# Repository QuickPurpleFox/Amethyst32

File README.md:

# Amethyst32
6502 based computer with 32kb of ram memory, with video based on tms9918 and sound on ym3812

## License

[MIT](https://choosealicense.com/licenses/mit/)

## Authors

- [@QuickPurpleFox](https://github.com/QuickPurpleFox) | Daniel K

supported by

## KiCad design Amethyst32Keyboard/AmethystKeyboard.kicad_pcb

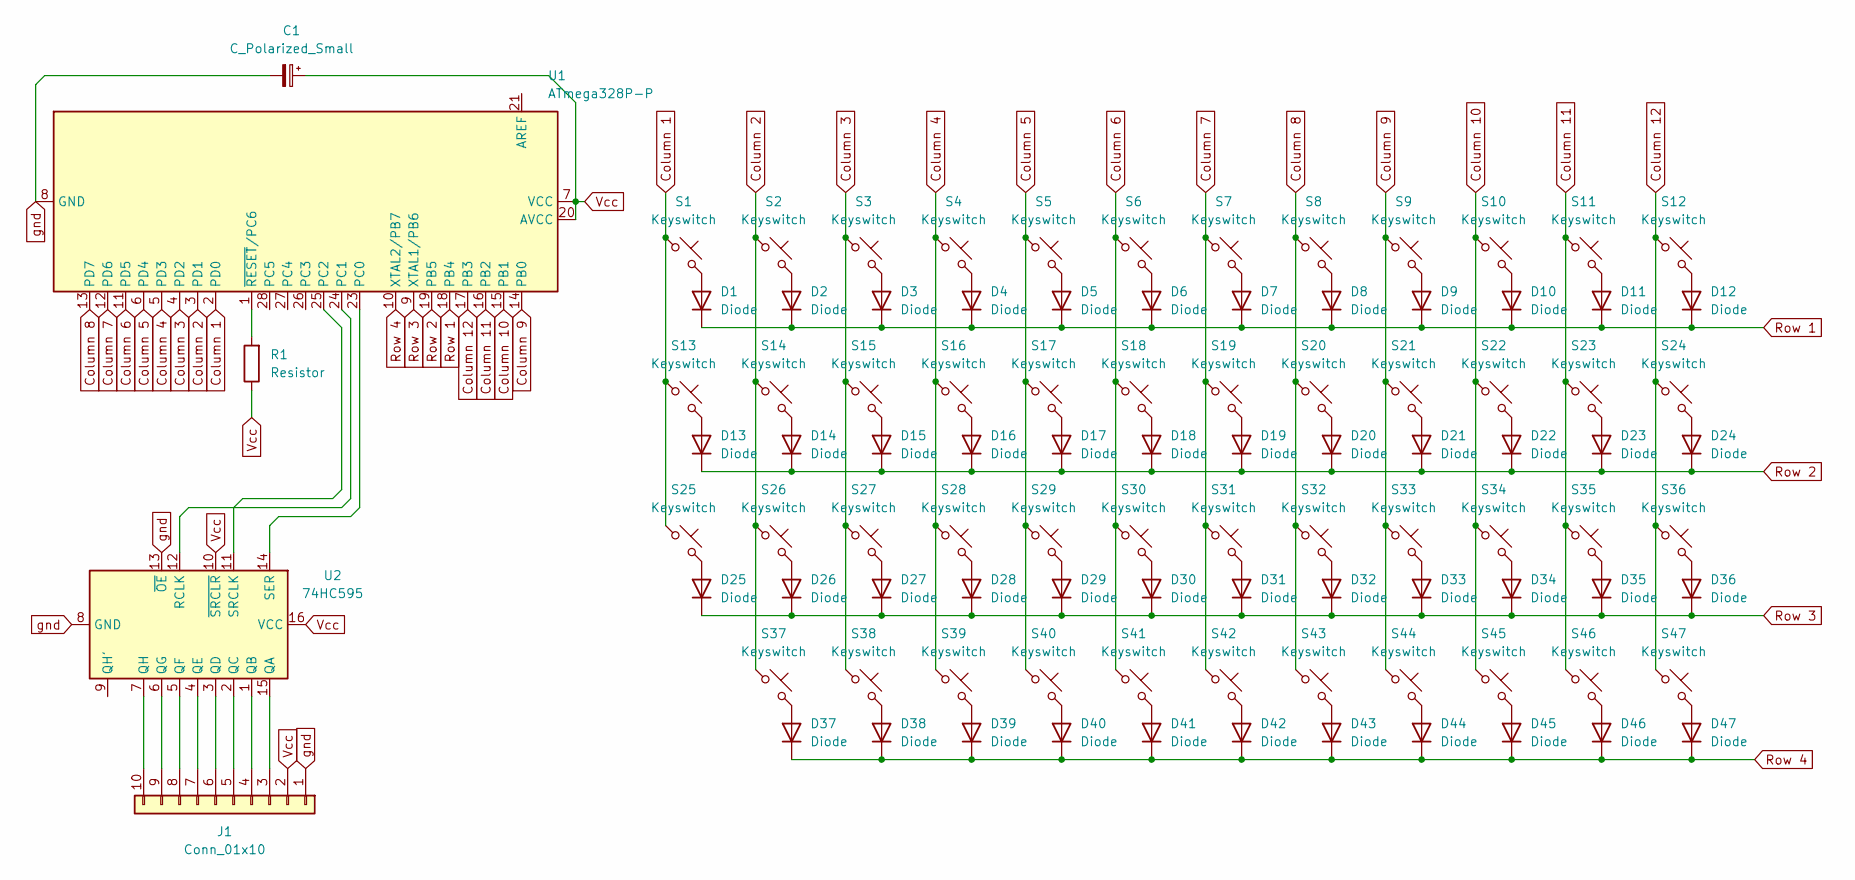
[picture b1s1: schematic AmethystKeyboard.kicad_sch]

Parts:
C1: C_Polarized_Small; CP_Radial_D5.0mm_P2.50mm
D1, D2, D3, D4, D5, D6, D7, D8, D9, D10, D11, D12, D13, D14, D15, D16, D17, D18, D19, D20, D21, D22, D23, D24, D25, D26, D27, D28, D29, D30, D31, D32, D33, D34, D35, D36, D37, D38, D39, D40, D41, D42, D43, D44, D45, D46, D47: Diode; Diode_DO-35
J1: Conn_01x10; PinHeader_1x10_P2.54mm_Vertical
R1: Resistor; R_Axial_DIN0207_L6.3mm_D2.5mm_P7.62mm_Horizontal
S1, S2, S3, S4, S5, S6, S7, S8, S9, S10, S11, S12, S13, S14, S15, S16, S17, S18, S19, S20, S21, S22, S23, S24, S25, S26, S27, S28, S29, S30, S31, S32, S33, S34, S35, S36, S38, S39, S40, S41, S42, S43, S44, S45, S46, S47: Keyswitch; MX_PCB_1.00u
S37: Keyswitch; MX_PCB_2.00u
U1: ATmega328P-P; DIP-28_W7.62mm
U2: 74HC595; DIP-16_W7.62mm

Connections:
Column 1: S1.1, S13.1, S25.1, U1.2 (PD0)
Column 2: S2.1, S14.1, S26.1, S37.1, U1.3 (PD1)
Column 3: S3.1, S15.1, S27.1, S38.1, U1.4 (PD2)
Column 4: S4.1, S16.1, S28.1, S39.1, U1.5 (PD3)
Column 5: S5.1, S17.1, S29.1, S40.1, U1.6 (PD4)
Column 6: S6.1, S18.1, S30.1, S41.1, U1.11 (PD5)
Column 7: S7.1, S19.1, S31.1, S42.1, U1.12 (PD6)
Column 8: S8.1, S20.1, S32.1, S43.1, U1.13 (PD7)
Column 9: S9.1, S21.1, S33.1, S44.1, U1.14 (PB0)
Column 10: S10.1, S22.1, S34.1, S45.1, U1.15 (PB1)
Column 11: S11.1, S23.1, S35.1, S46.1, U1.16 (PB2)
Column 12: S12.1, S24.1, S36.1, S47.1, U1.17 (PB3)
unnamed: D1.2 (A), S1.2
unnamed: D2.2 (A), S2.2
unnamed: D3.2 (A), S3.2
unnamed: D4.2 (A), S4.2
unnamed: D5.2 (A), S5.2
unnamed: D6.2 (A), S6.2
unnamed: D7.2 (A), S7.2
unnamed: D8.2 (A), S8.2
unnamed: D9.2 (A), S9.2
unnamed: D10.2 (A), S10.2
unnamed: D11.2 (A), S11.2
unnamed: D12.2 (A), S12.2
unnamed: D13.2 (A), S13.2
unnamed: D14.2 (A), S14.2
unnamed: D15.2 (A), S15.2
unnamed: D16.2 (A), S16.2
unnamed: D17.2 (A), S17.2
unnamed: D18.2 (A), S18.2
unnamed: D19.2 (A), S19.2
unnamed: D20.2 (A), S20.2
unnamed: D21.2 (A), S21.2
unnamed: D22.2 (A), S22.2
unnamed: D23.2 (A), S23.2
unnamed: D24.2 (A), S24.2
unnamed: D25.2 (A), S25.2
unnamed: D26.2 (A), S26.2
unnamed: D27.2 (A), S27.2
unnamed: D28.2 (A), S28.2
unnamed: D29.2 (A), S29.2
unnamed: D30.2 (A), S30.2
unnamed: D31.2 (A), S31.2
unnamed: D32.2 (A), S32.2
unnamed: D33.2 (A), S33.2
unnamed: D34.2 (A), S34.2
unnamed: D35.2 (A), S35.2
unnamed: D36.2 (A), S36.2
unnamed: D37.2 (A), S37.2
unnamed: D38.2 (A), S38.2
unnamed: D39.2 (A), S39.2
unnamed: D40.2 (A), S40.2
unnamed: D41.2 (A), S41.2
unnamed: D42.2 (A), S42.2
unnamed: D43.2 (A), S43.2
unnamed: D44.2 (A), S44.2
unnamed: D45.2 (A), S45.2
unnamed: D46.2 (A), S46.2
unnamed: D47.2 (A), S47.2
unnamed: J1.3, U2.15 (QA)
unnamed: J1.4, U2.1 (QB)
unnamed: J1.5, U2.2 (QC)
unnamed: J1.6, U2.3 (QD)
unnamed: J1.7, U2.4 (QE)
unnamed: J1.8, U2.5 (QF)
unnamed: J1.9, U2.6 (QG)
unnamed: J1.10, U2.7 (QH)
unnamed: U1.23 (PC0), U2.14 (SER)
unnamed: U1.24 (PC1), U2.12 (RCLK)
unnamed: U1.25 (PC2), U2.11 (SRCLK)
unnamed: R1.2, U1.1 (~RESET/PC6)
Row 1: D1.1 (K), D2.1 (K), D3.1 (K), D4.1 (K), D5.1 (K), D6.1 (K), D7.1 (K), D8.1 (K), D9.1 (K), D10.1 (K), D11.1 (K), D12.1 (K), U1.18 (PB4)
Row 2: D13.1 (K), D14.1 (K), D15.1 (K), D16.1 (K), D17.1 (K), D18.1 (K), D19.1 (K), D20.1 (K), D21.1 (K), D22.1 (K), D23.1 (K), D24.1 (K), U1.19 (PB5)
Row 3: D25.1 (K), D26.1 (K), D27.1 (K), D28.1 (K), D29.1 (K), D30.1 (K), D31.1 (K), D32.1 (K), D33.1 (K), D34.1 (K), D35.1 (K), D36.1 (K), U1.9 (XTAL1/PB6)
Row 4: D37.1 (K), D38.1 (K), D39.1 (K), D40.1 (K), D41.1 (K), D42.1 (K), D43.1 (K), D44.1 (K), D45.1 (K), D46.1 (K), D47.1 (K), U1.10 (XTAL2/PB7)
Vcc: C1.1, J1.2, R1.1, U1.7 (VCC), U1.20 (AVCC), U2.10 (~SRCLR), U2.16 (VCC)
gnd: C1.2, J1.1, U1.8 (GND), U1.22 (GND), U2.8 (GND), U2.13 (~OE)

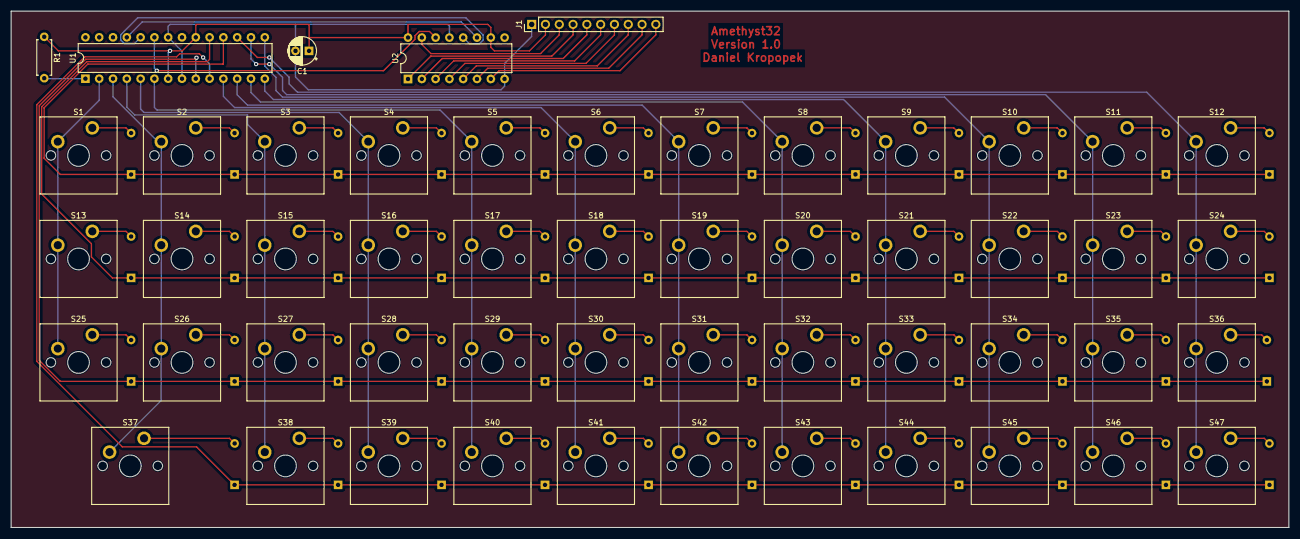
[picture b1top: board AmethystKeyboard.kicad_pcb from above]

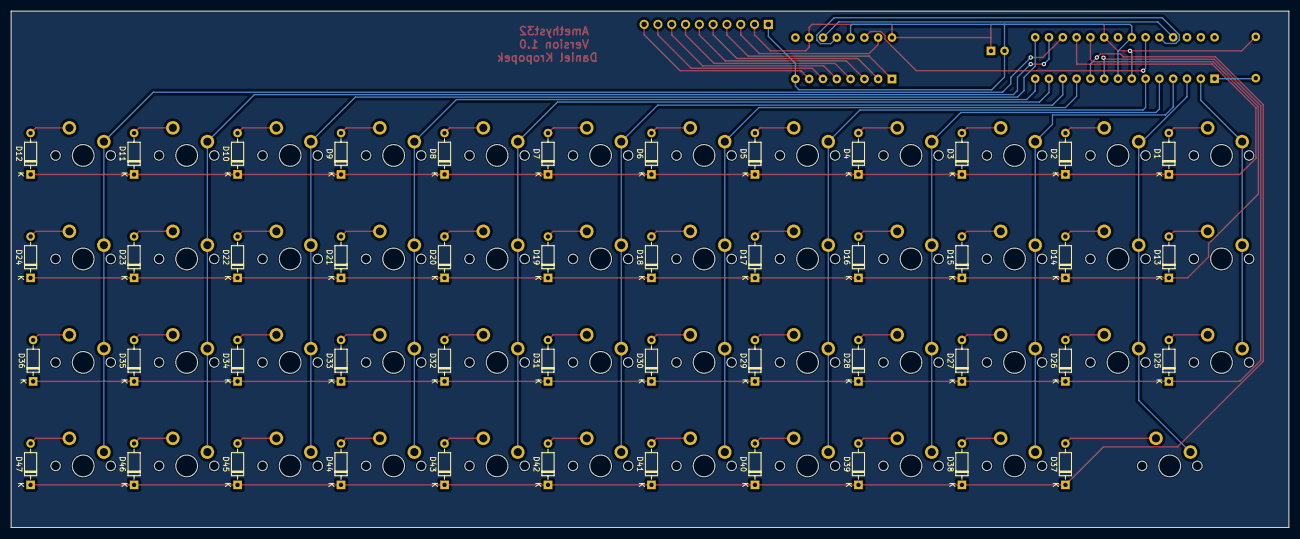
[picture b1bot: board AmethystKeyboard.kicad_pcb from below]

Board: 2 copper layers, 235.2 x 95.1 mm, 99 parts (47 on the bottom side), 77 nets.

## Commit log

2024-02-25 keyboard PCB
2024-12-09 Added LaTex backup
